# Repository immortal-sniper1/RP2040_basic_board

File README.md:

# RP2040_board1
 RP2040 test board, breadboard friedly.
 /
 Features: 
  /
 -Li ion power optin (protection built in) auto switching power in case of usb unpluging 
  /
 -RTC with separate 20mm cell  
 -microSD card slot  
 -all pins exposed (that are not used internaly for a dedicated task)  
 -both LDO and buck switching convertor for power, one of them may be used based on the SPDT switch  
 (later maybe just one of them may be populated and the switch replaced by a solder bridge)  
 -same pinout as rpi pico just wider form factor 
 -all pins labeled 
 -It requires a few extra wires to work since this is a 2 layer design and this was a scarifice
made in order to keep a solid ground plane under the entire PCB 
 
 Images:  https://imgur.com/a/X6zGeTy

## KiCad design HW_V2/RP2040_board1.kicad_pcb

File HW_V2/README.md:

# RP2040_board1
 RP2040 test board, breadboard friedly.  
 Features:   
 -Li ion power optin (protection built in) auto switching power in case of usb unpluging   
 -RTC with separate 20mm cell  
 -microSD card slot  
 -all pins exposed (that are not used internaly for a dedicated task)  
 -both LDO and buck switching convertor for power, one of them may be used based on the SPDT switch   
 (later maybe just one of them may be populated and the switch replaced by a solder bridge)   
 -same pinout as rpi pico just wider form factor   
 -all pins labeled   
 -It requires a few extra wires to work since this is a 2 layer design and this was a scarifice 
made in order to keep a solid ground plane under the entire PCB   
 
 Images:  https://imgur.com/a/X6zGeTy

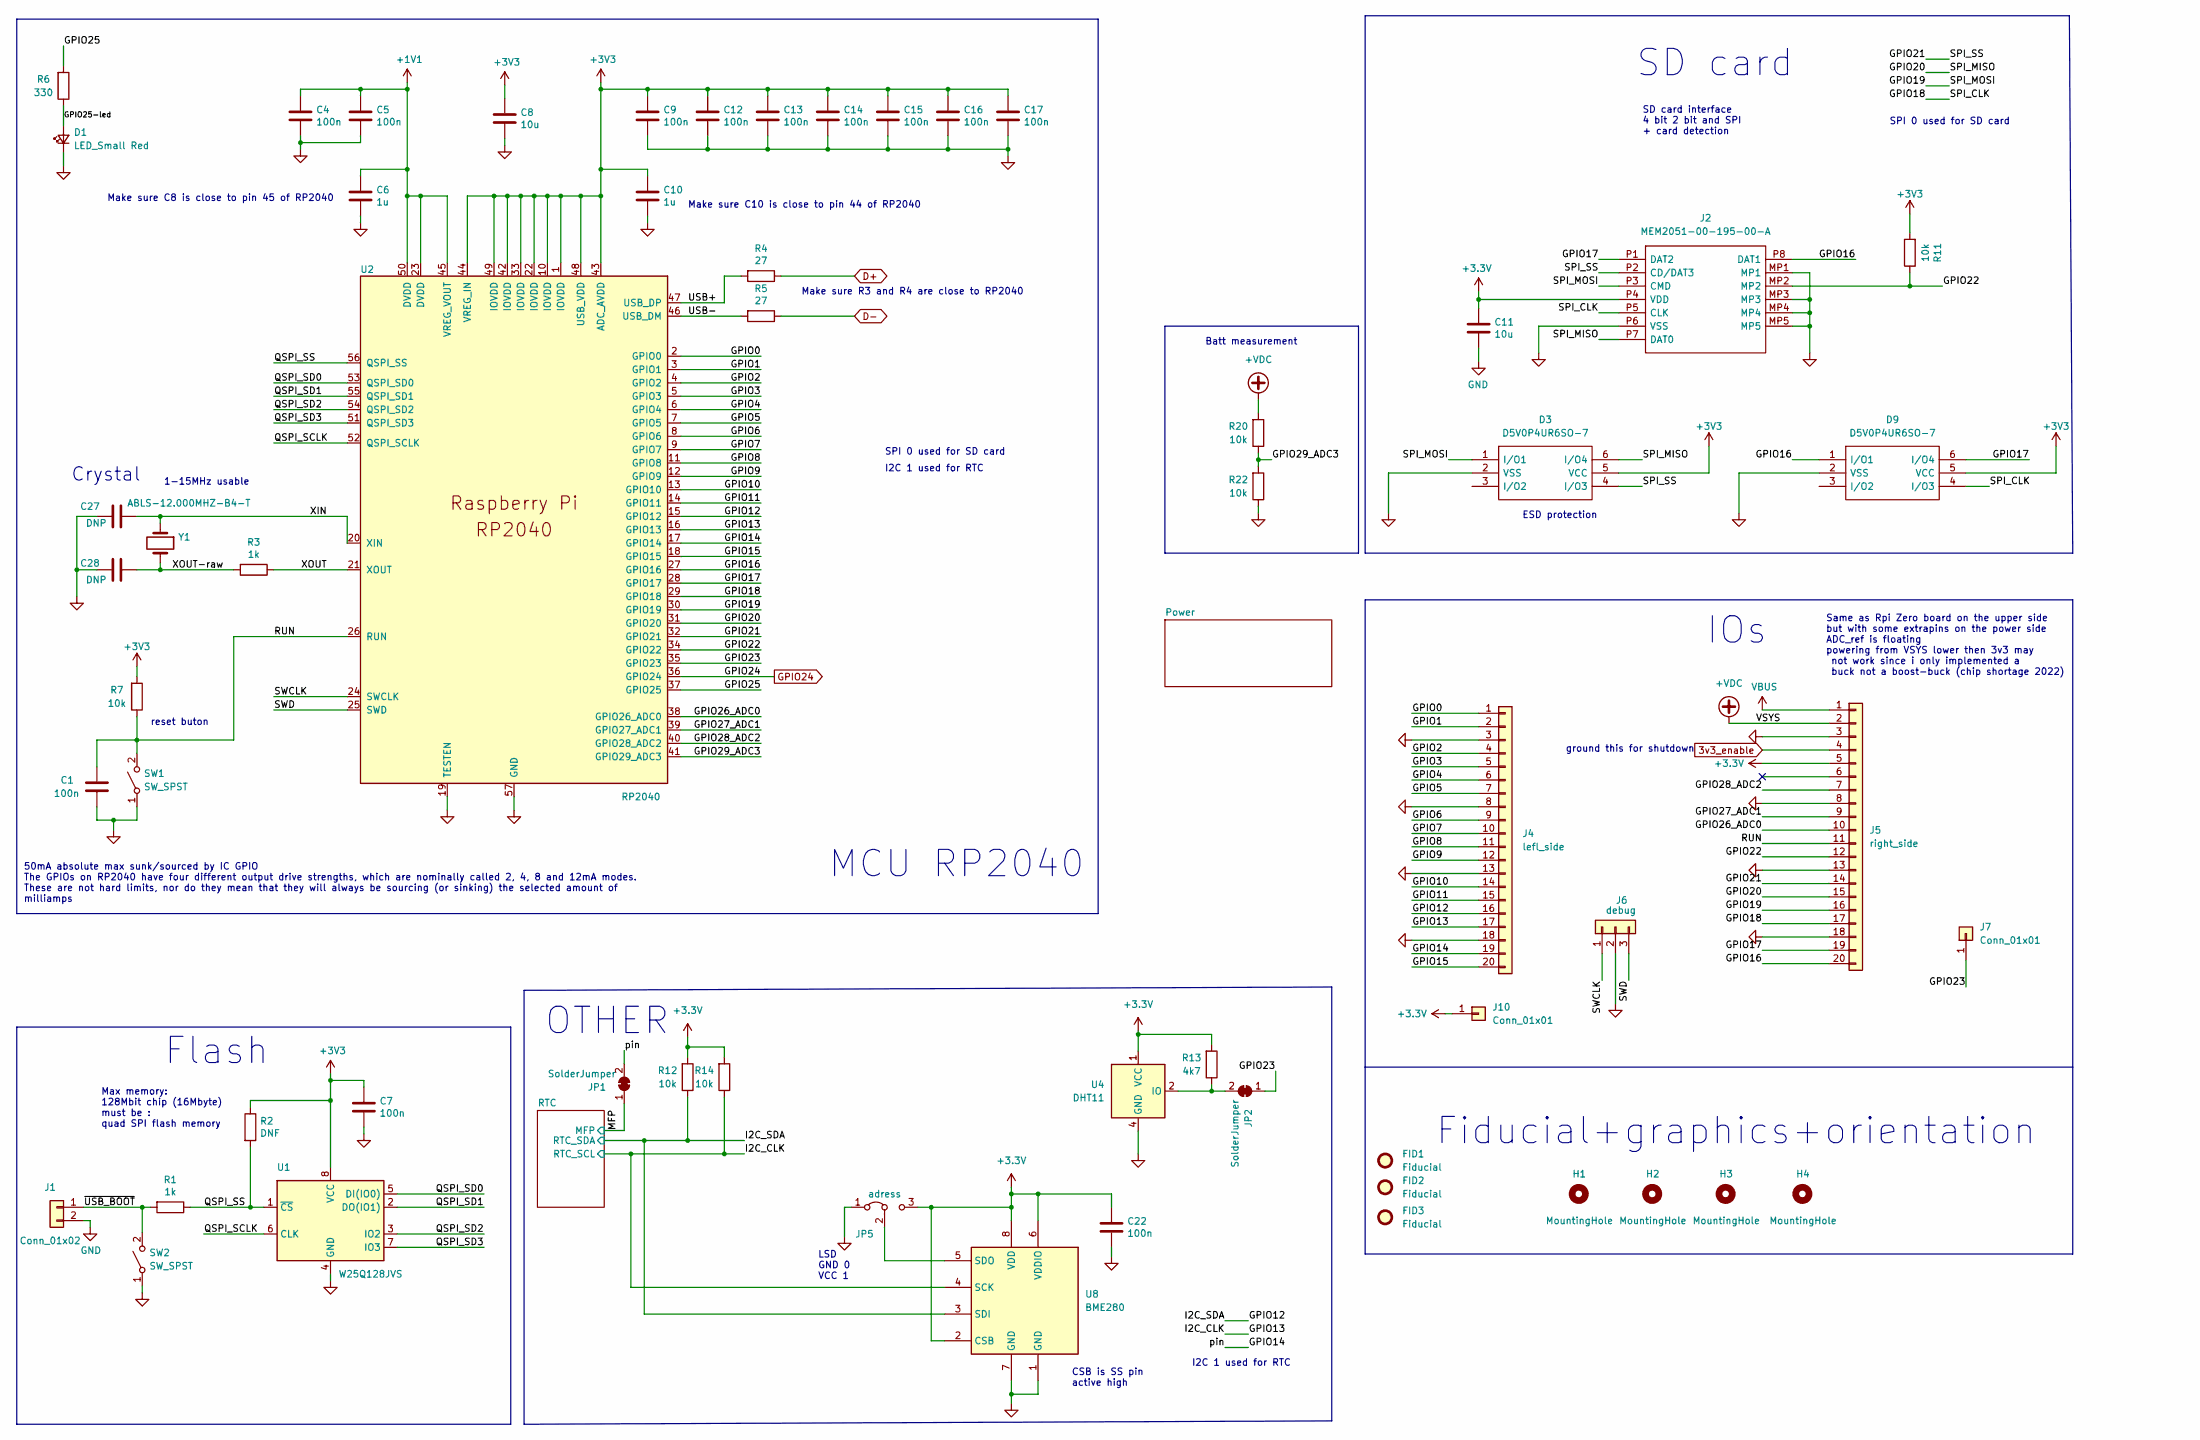
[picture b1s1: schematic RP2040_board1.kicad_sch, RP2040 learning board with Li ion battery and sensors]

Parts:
C1, C4, C5, C7, C9, C12, C13, C14, C15, C16, C17, C22: 100n; C_0805_2012Metric_Pad1.18x1.45mm_HandSolder
C6, C10: 1u; C_0805_2012Metric_Pad1.18x1.45mm_HandSolder
C8: 10u; C_0805_2012Metric_Pad1.18x1.45mm_HandSolder
C11: 10u; C_0603_1608Metric_Pad1.08x0.95mm_HandSolder
C27, C28: DNP; C_0805_2012Metric_Pad1.18x1.45mm_HandSolder
D1: LED_Small Red; LED_0603_1608Metric_Pad1.05x0.95mm_HandSolder
D3, D9: D5V0P4UR6SO-7; SOT95P285X140-6N; Mouser Part Number 621-D5V0P4UR6SO-7
FID1: Fiducial; Fiducial_0.5mm_Mask1mm
FID2: Fiducial; KiCad-Logo2_8mm_SilkScreen
FID3: Fiducial; OSHW-Logo2_14.6x12mm_SilkScreen
H1, H2, H3, H4: MountingHole; MountingHole_3.2mm_M3
J1: Conn_01x02; PinHeader_1x02_P2.54mm_Vertical
J2: MEM2051-00-195-00-A; MEM20510019500A; Mouser Part Number 640-MEM20510019500A
J4: lefl_side; PinSocket_1x20_P2.54mm_Vertical
J5: right_side; PinSocket_1x20_P2.54mm_Vertical
J6: debug; PinSocket_1x03_P2.54mm_Vertical
J7, J10: Conn_01x01; PinSocket_1x01_P2.54mm_Vertical
JP1, JP2: SolderJumper; SolderJumper-2_P1.3mm_Bridged_RoundedPad1.0x1.5mm
JP5: adress; SolderJumper-3_P1.3mm_Bridged12_RoundedPad1.0x1.5mm
R1, R3: 1k; R_0603_1608Metric_Pad0.98x0.95mm_HandSolder
R2: DNF; R_0603_1608Metric_Pad0.98x0.95mm_HandSolder
R4, R5: 27; R_0603_1608Metric_Pad0.98x0.95mm_HandSolder
R6: 330; R_0603_1608Metric_Pad0.98x0.95mm_HandSolder
R7, R11, R12, R14, R20, R22: 10k; R_0603_1608Metric_Pad0.98x0.95mm_HandSolder
R13: 4k7; R_0603_1608Metric_Pad0.98x0.95mm_HandSolder
SW1, SW2: SW_SPST; PTS526SK15SMTR2LFS
U1: W25Q128JVS; SOIC-8_5.23x5.23mm_P1.27mm
U2: RP2040; RP2040-QFN-56
U4: DHT11; Aosong_DHT11_5.5x12.0_P2.54mm
U8: BME280; Bosch_LGA-8_2.5x2.5mm_P0.65mm_ClockwisePinNumbering
Y1: ABLS-12.000MHZ-B4-T; ATS120SM

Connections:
3v3_enable: J5.4; also elsewhere on the board
+1V1: C4.1, C5.1, C6.1, U2.23 (DVDD), U2.45 (VREG_VOUT), U2.50 (DVDD)
+VDC: J5.2, R20.2; also elsewhere on the board
/GPIO0: J4.1, U2.2 (GPIO0)
/GPIO1: J4.2, U2.3 (GPIO1)
/GPIO2: J4.4, U2.4 (GPIO2)
/GPIO3: J4.5, U2.5 (GPIO3)
/GPIO4: J4.6, U2.6 (GPIO4)
/GPIO5: J4.7, U2.7 (GPIO5)
/GPIO6: J4.9, U2.8 (GPIO6)
/GPIO7: J4.10, U2.9 (GPIO7)
/GPIO8: J4.11, U2.11 (GPIO8)
/GPIO9: J4.12, U2.12 (GPIO9)
/GPIO10: J4.14, U2.13 (GPIO10)
/GPIO11: J4.15, U2.14 (GPIO11)
/GPIO12: J4.16, R12.1, U2.15 (GPIO12), U8.3 (SDI); also elsewhere on the board
/GPIO13: J4.17, R14.1, U2.16 (GPIO13), U8.4 (SCK); also elsewhere on the board
/GPIO14: J4.19, JP1.2 (B), U2.17 (GPIO14)
/GPIO15: J4.20, U2.18 (GPIO15)
/GPIO16: D9.1 (I/O1), J2.P8 (DAT1), J5.20, U2.27 (GPIO16)
/GPIO17: D9.6 (I/O4), J2.P1 (DAT2), J5.19, U2.28 (GPIO17)
/GPIO18: D9.4 (I/O3), J2.P5 (CLK), J5.17, U2.29 (GPIO18)
/GPIO19: D3.1 (I/O1), J2.P3 (CMD), J5.16, U2.30 (GPIO19)
/GPIO20: D3.6 (I/O4), J2.P7 (DAT0), J5.15, U2.31 (GPIO20)
/GPIO21: D3.4 (I/O3), J2.P2 (CD/DAT3), J5.14, U2.32 (GPIO21)
/GPIO22: J2.MP2, J5.12, R11.1, U2.34 (GPIO22)
/GPIO23: J7.1, JP2.1 (A), U2.35 (GPIO23)
/GPIO25: R6.2, U2.37 (GPIO25)
/GPIO25-led: D1.2 (A), R6.1
/GPIO26_ADC0: J5.10, U2.38 (GPIO26_ADC0)
/GPIO27_ADC1: J5.9, U2.39 (GPIO27_ADC1)
/GPIO28_ADC2: J5.7, U2.40 (GPIO28_ADC2)
/GPIO29_ADC3: R20.1, R22.2, U2.41 (GPIO29_ADC3)
/MFP: JP1.1 (A); also elsewhere on the board
/QSPI_SCLK: U1.6 (CLK), U2.52 (QSPI_SCLK)
/QSPI_SD0: U1.5 (DI(IO0)), U2.53 (QSPI_SD0)
/QSPI_SD1: U1.2 (DO(IO1)), U2.55 (QSPI_SD1)
/QSPI_SD2: U1.3 (IO2), U2.54 (QSPI_SD2)
/QSPI_SD3: U1.7 (IO3), U2.51 (QSPI_SD3)
/QSPI_SS: R1.1, R2.2, U1.1 (~CS), U2.56 (QSPI_SS)
/RUN: C1.1, J5.11, R7.1, SW1.2 (B), U2.26 (RUN)
/SWCLK: J6.1, U2.24 (SWCLK)
/SWD: J6.3, U2.25 (SWD)
/USB+: R4.2, U2.47 (USB_DP)
/USB-: R5.2, U2.46 (USB_DM)
/XIN: C27.2, U2.20 (XIN), Y1.1
/XOUT: R3.1, U2.21 (XOUT)
/XOUT-raw: C28.2, R3.2, Y1.2
/~USB_BOOT: J1.1, R1.2, SW2.2 (B)
D+: R4.1; also elsewhere on the board
D-: R5.1; also elsewhere on the board
GND: C1.2, C4.2, C5.2, C6.2, C7.2, C8.2, C9.2, C10.2, C11.2, C12.2, C13.2, C14.2, C15.2, C16.2, C17.2, C22.2, C27.1, C28.1, D1.1 (K), D3.2 (VSS), D9.2 (VSS), J1.2, J2.MP1, J2.MP3, J2.MP4, J2.MP5, J2.P6 (VSS), J4.3, J4.8, J4.13, J4.18, J5.3, J5.8, J5.13, J5.18, J6.2, JP5.1 (A), R22.1, SW1.1 (A), SW2.1 (A), U1.4 (GND), U2.19 (TESTEN), U2.57 (GND), U4.4 (GND), U8.1 (GND), U8.7 (GND); also elsewhere on the board
GPIO24: U2.36 (GPIO24); also elsewhere on the board
unnamed: JP2.2 (B), R13.1, U4.2 (IO)
unnamed: JP5.2 (C), U8.5 (SDO)
VBUS: J5.1; also elsewhere on the board

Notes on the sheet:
I2C 1 used for RTC
Fiducial+graphics+orientation
SD card interface 4 bit 2 bit and SPI + card detection
OTHER
50mA absolute max sunk/sourced by IC GPIO The GPIOs on RP2040 have four different output drive strengths, which are nominally called 2, 4, 8 and 12mA modes. These are not hard limits, nor do they mean that they will always be sourcing (or sinking) the selected amount of milliamps
IOs
Same as Rpi Zero board on the upper side but with some extrapins on the power side ADC_ref is floating powering from VSYS lower then 3v3 may not work since i only implemented a buck not a boost-buck (chip shortage 2022)
Flash
ground this for shutdown
Crystal
SD card
MCU RP2040
Make sure C8 is close to pin 45 of RP2040
SPI 0 used for SD card
Make sure R3 and R4 are close to RP2040
Max memory: 128Mbit chip (16Mbyte) must be : quad SPI flash memory
1-15MHz usable
Make sure C10 is close to pin 44 of RP2040
reset buton
LSD GND 0 VCC 1
ESD protection
Batt measurement
CSB is SS pin active high

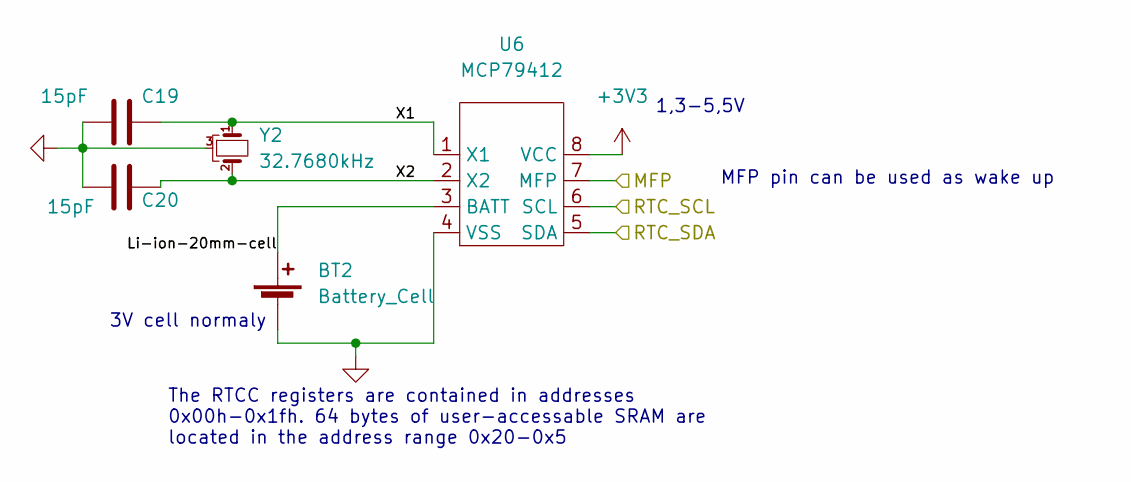
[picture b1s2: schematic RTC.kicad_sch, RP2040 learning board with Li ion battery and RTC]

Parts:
BT2: Battery_Cell; BATHLD001THM
C19, C20: 15pF; C_0603_1608Metric_Pad1.08x0.95mm_HandSolder
U6: MCP79412; TSSOP-8_4.4x3mm_P0.65mm
Y2: 32.7680kHz; Crystal_C38-LF_D3.0mm_L8.0mm_Vertical

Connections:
/GPIO12: U6.5 (SDA); also elsewhere on the board
/GPIO13: U6.6 (SCL); also elsewhere on the board
/MFP: U6.7 (MFP); also elsewhere on the board
/RTC/Li-ion-20mm-cell: BT2.1 (+), U6.3 (BATT)
/RTC/X1: C19.2, U6.1 (X1), Y2.1
/RTC/X2: C20.2, U6.2 (X2), Y2.2
GND: BT2.2 (-), C19.1, C20.1, U6.4 (VSS), Y2.3; also elsewhere on the board

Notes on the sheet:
1,3-5,5V
3V cell normaly
MFP pin can be used as wake up
The RTCC registers are contained in addresses 0x00h-0x1fh. 64 bytes of user-accessable SRAM are located in the address range 0x20-0x5

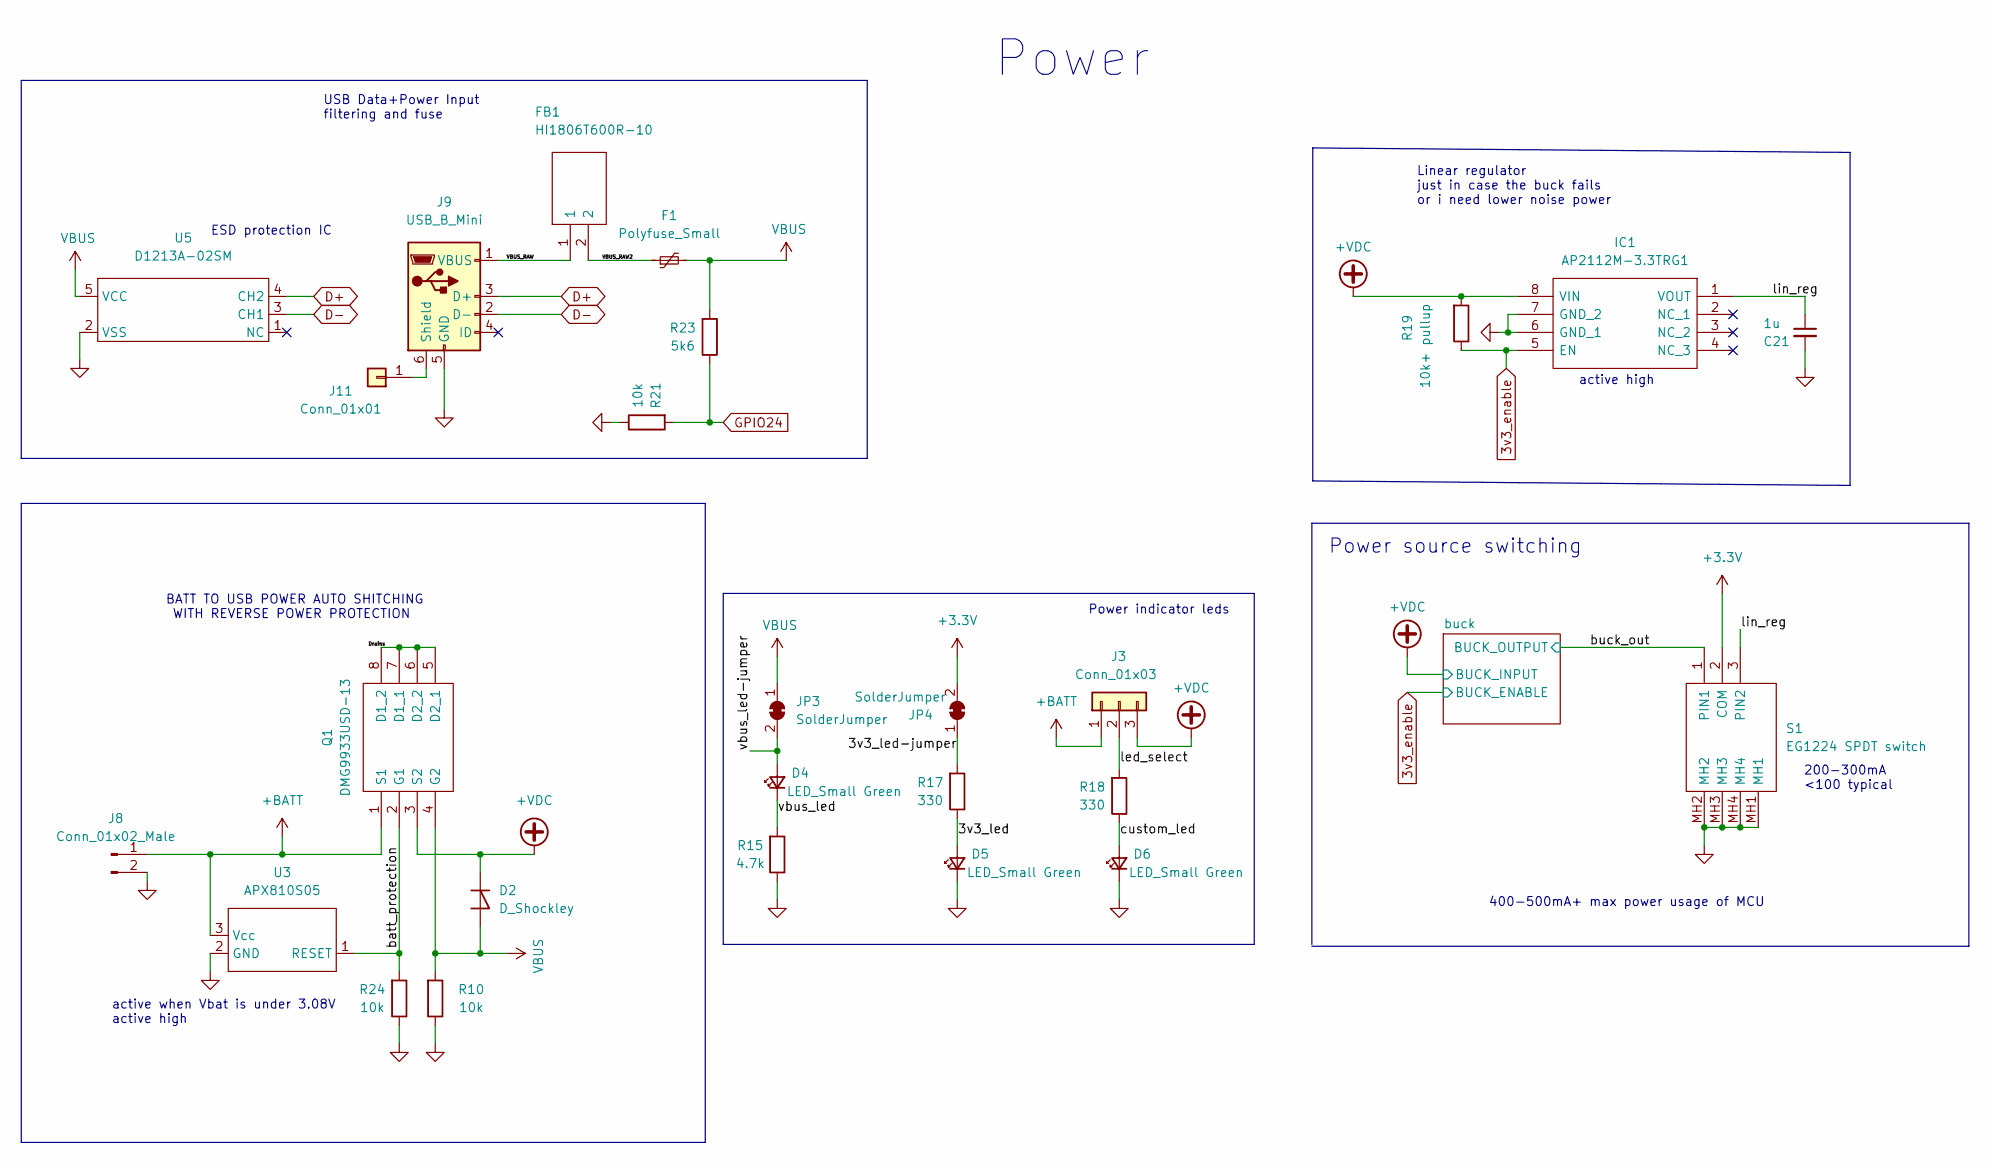
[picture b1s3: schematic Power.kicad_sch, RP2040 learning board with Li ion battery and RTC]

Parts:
C21: 1u; C_0805_2012Metric_Pad1.18x1.45mm_HandSolder
D2: D_Shockley; D_DO-15_P5.08mm_Vertical_KathodeUp
D4, D5, D6: LED_Small Green; LED_0603_1608Metric_Pad1.05x0.95mm_HandSolder
F1: Polyfuse_Small; Fuse_1812_4532Metric_Pad1.30x3.40mm_HandSolder
FB1: HI1806T600R-10; BEADC4516X185N; Mouser Part Number 875-HI1806T600R-10
IC1: AP2112M-3.3TRG1; SOIC127P600X170-8N; Mouser Part Number 621-AP2112M-3.3TRG1
J3: Conn_01x03; PinHeader_1x03_P2.54mm_Vertical
J8: Conn_01x02_Male; PinHeader_1x02_P2.54mm_Vertical
J9: USB_B_Mini; USB_Mini-B_Lumberg_2486_01_Horizontal
J11: Conn_01x01; PinSocket_1x01_P2.54mm_Vertical
JP3, JP4: SolderJumper; SolderJumper-2_P1.3mm_Bridged_RoundedPad1.0x1.5mm
Q1: DMG9933USD-13; SOIC127P600X175-8N; Mouser Part Number 621-DMG9933USD-13
R10, R21, R24: 10k; R_0603_1608Metric_Pad0.98x0.95mm_HandSolder
R15: 4.7k; R_Axial_DIN0204_L3.6mm_D1.6mm_P5.08mm_Vertical
R17, R18: 330; R_0603_1608Metric_Pad0.98x0.95mm_HandSolder
R19: 10k+ pullup; R_0603_1608Metric_Pad0.98x0.95mm_HandSolder
R23: 5k6; R_0603_1608Metric_Pad0.98x0.95mm_HandSolder
S1: EG1224 SPDT switch; EG1224; Mouser Part Number 612-EG1224
U3: APX810S05; SOT-23
U5: D1213A-02SM; SOT-23-5_HandSoldering

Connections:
3v3_enable: IC1.5 (EN), R19.1; also elsewhere on the board
+BATT: J3.1, J8.1, Q1.1 (S1), U3.3 (Vcc); also elsewhere on the board
+VDC: D2.1 (K), IC1.8 (VIN), J3.3, Q1.3 (S2), R19.2; also elsewhere on the board
/Power/3v3_led: D5.2 (A), R17.1
/Power/3v3_led-jumper: JP4.1 (A), R17.2
/Power/VBUS_RAW: FB1.1, J9.1 (VBUS)
/Power/VBUS_RAW2: F1.1, FB1.2
/Power/batt_protection: Q1.2 (G1), R24.2, U3.1 (RESET); also elsewhere on the board
/Power/buck_out: S1.1 (PIN1); also elsewhere on the board
/Power/custom_led: D6.2 (A), R18.1
/Power/led_select: J3.2, R18.2
/Power/lin_reg: C21.1, IC1.1 (VOUT), S1.3 (PIN2)
/Power/vbus_led: D4.1 (K), R15.2
/Power/vbus_led-jumper: D4.2 (A), JP3.2 (B)
D+: J9.3 (D+), U5.4 (CH2); also elsewhere on the board
D-: J9.2 (D-), U5.3 (CH1); also elsewhere on the board
GND: C21.2, D5.1 (K), D6.1 (K), IC1.6 (GND_1), IC1.7 (GND_2), J8.2, J9.5 (GND), R10.1, R15.1, R21.1, R24.1, S1.MH1, S1.MH2, S1.MH3, S1.MH4, U3.2 (GND), U5.2 (VSS); also elsewhere on the board
GPIO24: R21.2, R23.1; also elsewhere on the board
unnamed: J9.6 (Shield), J11.1
unnamed: Q1.5 (D2_1), Q1.6 (D2_2), Q1.7 (D1_1), Q1.8 (D1_2)
VBUS: D2.2 (A), F1.2, JP3.1 (A), Q1.4 (G2), R10.2, R23.2, U5.5 (VCC); also elsewhere on the board

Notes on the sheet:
400-500mA+ max power usage of MCU
ESD protection IC
active when Vbat is under 3.08V active high
Power indicator leds
Linear regulator just in case the buck fails or i need lower noise power
200-300mA <100 typical
USB Data+Power Input filtering and fuse
Power source switching
Power
active high
BATT TO USB POWER AUTO SHITCHING WITH REVERSE POWER PROTECTION

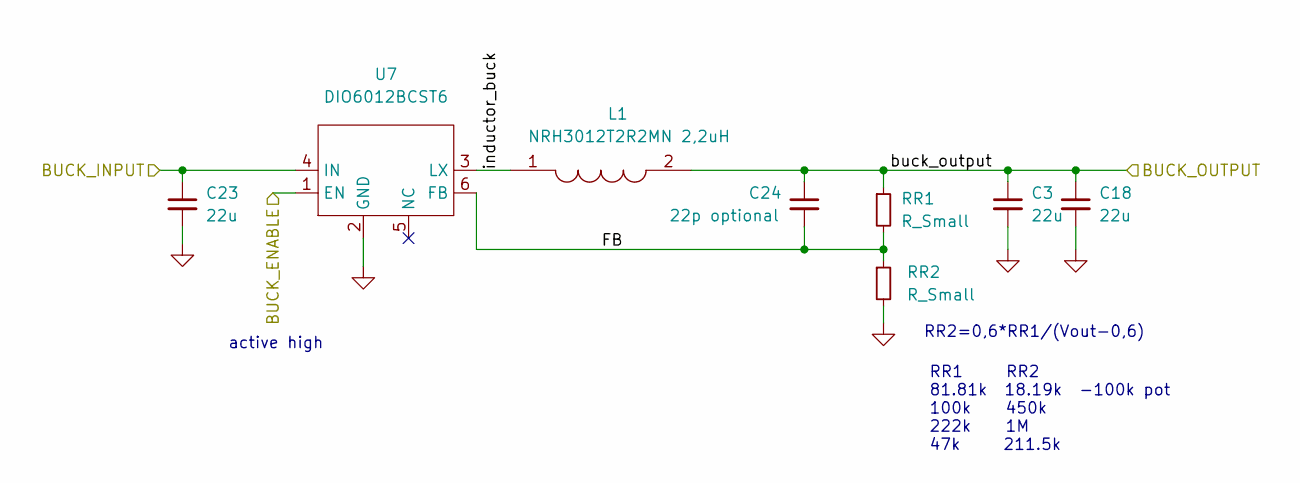
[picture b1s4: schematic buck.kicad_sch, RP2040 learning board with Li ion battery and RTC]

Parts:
C3, C18, C23: 22u; CP_Radial_D5.0mm_P2.00mm
C24: 22p optional; C_0603_1608Metric_Pad1.08x0.95mm_HandSolder
L1: NRH3012T2R2MN 2,2uH; NRH3012T220MNV; Mouser Part Number 963-NRH3012T2R2MN
RR1, RR2: R_Small; R_Axial_DIN0204_L3.6mm_D1.6mm_P5.08mm_Vertical
U7: DIO6012BCST6; SOT-23-6_Handsoldering

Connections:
3v3_enable: U7.1 (EN); also elsewhere on the board
+VDC: C23.1, U7.4 (IN); also elsewhere on the board
/Power/buck/FB: C24.2, RR1.2, RR2.1, U7.6 (FB)
/Power/buck/inductor_buck: L1.1, U7.3 (LX)
/Power/buck_out: C3.1, C18.1, C24.1, L1.2, RR1.1; also elsewhere on the board
GND: C3.2, C18.2, C23.2, RR2.2, U7.2 (GND); also elsewhere on the board

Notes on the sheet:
RR2=0,6*RR1/(Vout-0,6)
active high
RR1 RR2 81.81k 18.19k -100k pot 100k 450k 222k 1M 47k 211.5k

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
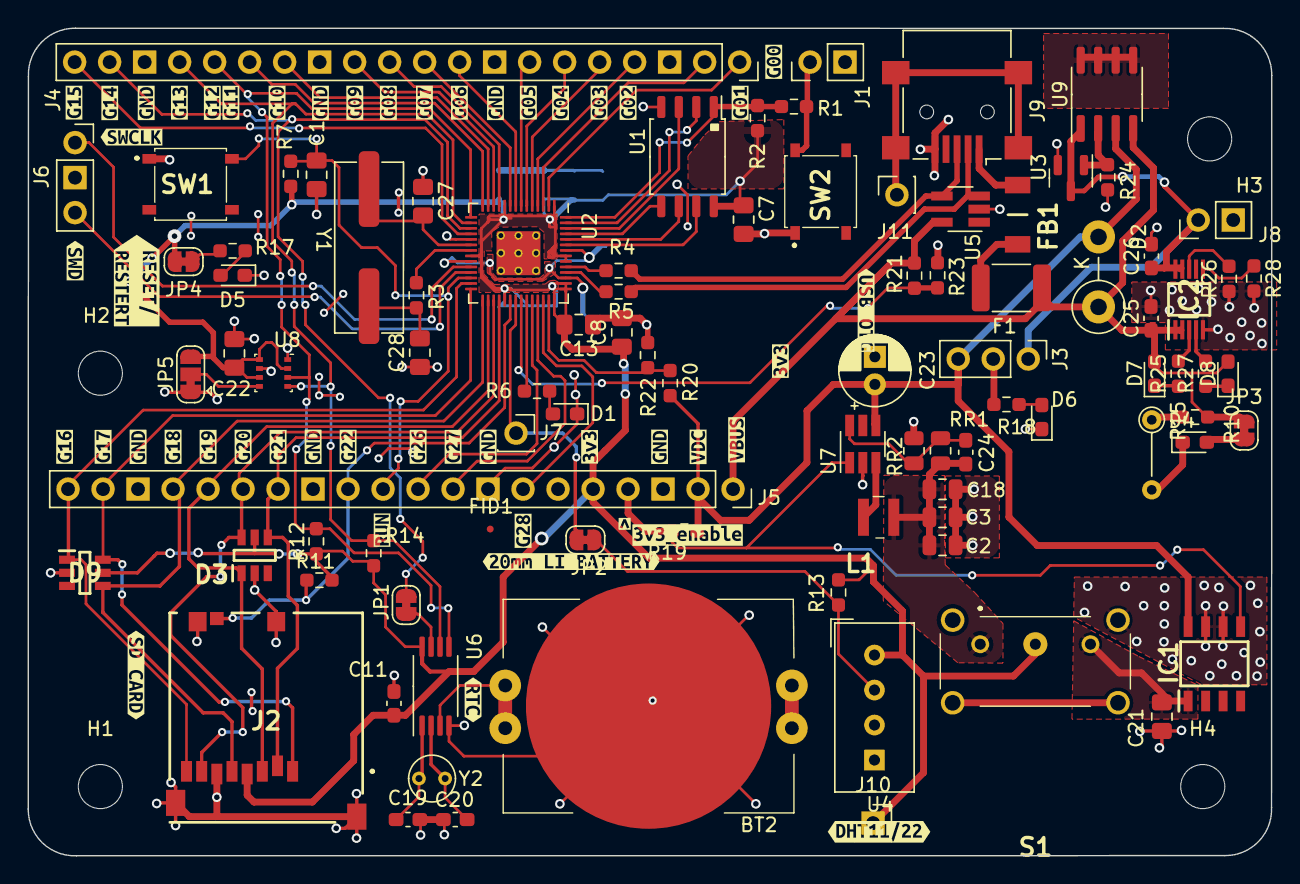
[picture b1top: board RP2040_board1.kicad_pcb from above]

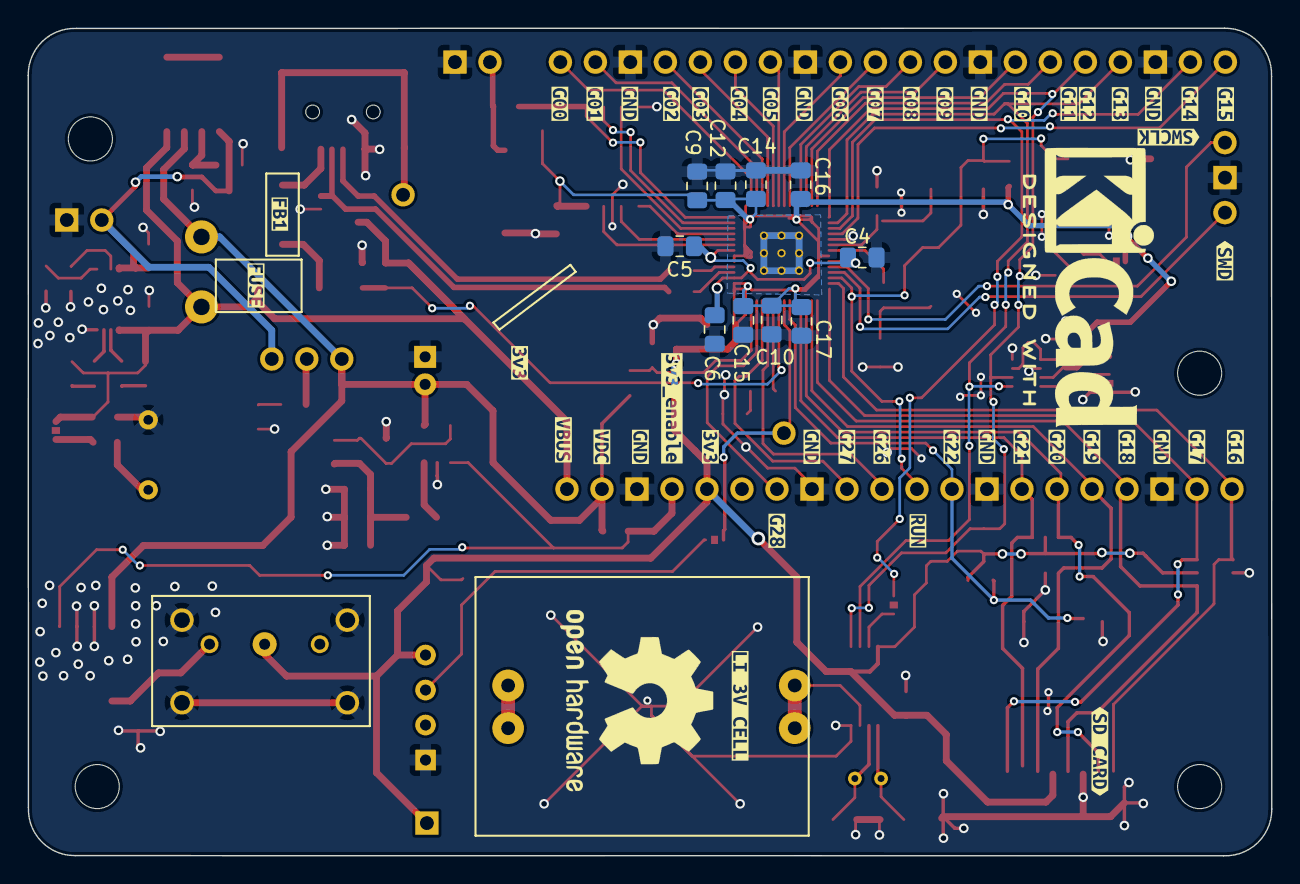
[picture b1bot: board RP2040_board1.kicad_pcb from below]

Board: 2 copper layers, 90.2 x 60.1 mm, 204 parts (61 on the bottom side), 82 nets.

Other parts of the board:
 : LOGO
C2: 10u; C_0805_2012Metric
C25: 1u; C_0603_1608Metric_Pad1.08x0.95mm_HandSolder
C26: 4.7u; C_0603_1608Metric_Pad1.08x0.95mm_HandSolder
D7, D8: LED_Small; LED_0603_1608Metric_Pad1.05x0.95mm_HandSolder
IC2: MCP73834T-FCI_UN; SOP50P490X110-10N
R25, R27: 470; R_0603_1608Metric_Pad0.98x0.95mm_HandSolder
R26, R28: 10k; R_0603_1608Metric_Pad0.98x0.95mm_HandSolder
U9: DMG9933USD-13; SOIC-8_3.9x4.9mm_P1.27mm
kibuzzard-626E75F6, kibuzzard-626E75F6#2: G***; kibuzzard-626E75F6
kibuzzard-626E76A5, kibuzzard-626E76A5#2: G***; kibuzzard-626E76A5
kibuzzard-626E76AE, kibuzzard-626E76AE#2: G***; kibuzzard-626E76AE
kibuzzard-626E76B5, kibuzzard-626E76B5#2: G***; kibuzzard-626E76B5
kibuzzard-626E76C0, kibuzzard-626E76C0#2: G***; kibuzzard-626E76C0
kibuzzard-626E76C6, kibuzzard-626E76C6#2: G***; kibuzzard-626E76C6
kibuzzard-626E76CD, kibuzzard-626E76CD#2: G***; kibuzzard-626E76CD
kibuzzard-626E76D2, kibuzzard-626E76D2#2: G***; kibuzzard-626E76D2
kibuzzard-626E76E0, kibuzzard-626E76E0#2: G***; kibuzzard-626E76E0
kibuzzard-626E76E7, kibuzzard-626E76E7#2: G***; kibuzzard-626E76E7
kibuzzard-626E94A4: G***; kibuzzard-626E94A4
kibuzzard-626E96A8, kibuzzard-626E96A8#2: G***; kibuzzard-626E96A8
kibuzzard-626E96B6, kibuzzard-626E96B6#2, kibuzzard-626E96B6#3, kibuzzard-626E96B6#4: G***; kibuzzard-626E96B6
kibuzzard-626E96C2, kibuzzard-626E96C2#2: G***; kibuzzard-626E96C2
kibuzzard-626E96E0: G***; kibuzzard-626E96E0
kibuzzard-626E96EE, kibuzzard-626E96EE#2: G***; kibuzzard-626E96EE
kibuzzard-626E96FC, kibuzzard-626E96FC#2: G***; kibuzzard-626E96FC
kibuzzard-626E98D2, kibuzzard-626E98D2#2: G***; kibuzzard-626E98D2
kibuzzard-626E760F, kibuzzard-626E760F#2: G***; kibuzzard-626E760F
kibuzzard-626E761A, kibuzzard-626E761A#2: G***; kibuzzard-626E761A
kibuzzard-626E769F, kibuzzard-626E769F#2: G***; kibuzzard-626E769F
kibuzzard-626E937A: G***; kibuzzard-626E937A
kibuzzard-626E946D: G***; kibuzzard-626E946D
kibuzzard-626E948F: G***; kibuzzard-626E948F
kibuzzard-626E966C, kibuzzard-626E966C#2: G***; kibuzzard-626E966C
kibuzzard-626E968A, kibuzzard-626E968A#2: G***; kibuzzard-626E968A
kibuzzard-626E969D, kibuzzard-626E969D#2: G***; kibuzzard-626E969D
kibuzzard-626E977A, kibuzzard-626E977A#2: G***; kibuzzard-626E977A
kibuzzard-626E7343, kibuzzard-626E7343#2: G***; kibuzzard-626E7343
kibuzzard-626E7607, kibuzzard-626E7607#2, kibuzzard-626E7607#3, kibuzzard-626E7607#4, kibuzzard-626E7607#5, kibuzzard-626E7607#6, kibuzzard-626E7607#7, kibuzzard-626E7607#8, kibuzzard-626E7607#9, kibuzzard-626E7607#10, kibuzzard-626E7607#11, kibuzzard-626E7607#12, kibuzzard-626E7607#13, kibuzzard-626E7607#14, kibuzzard-626E7607#15: G***; kibuzzard-626E7607
kibuzzard-626E7622, kibuzzard-626E7622#2: G***; kibuzzard-626E7622
kibuzzard-626E7694, kibuzzard-626E7694#2: G***; kibuzzard-626E7694
kibuzzard-626E9458, kibuzzard-626E9458#2: G***; kibuzzard-626E9458
kibuzzard-626E9527, kibuzzard-626E9527#2: G***; kibuzzard-626E9527
kibuzzard-626E9537, kibuzzard-626E9537#2: G***; kibuzzard-626E9537
kibuzzard-626E9677, kibuzzard-626E9677#2: G***; kibuzzard-626E9677
kibuzzard-626E9683, kibuzzard-626E9683#2: G***; kibuzzard-626E9683
kibuzzard-626E9692, kibuzzard-626E9692#2: G***; kibuzzard-626E9692
kibuzzard-626ED31B, kibuzzard-626ED31B#2: G***; kibuzzard-626ED31B
kibuzzard-626ED41E: G***; kibuzzard-626ED41E
kibuzzard-626ED45F: G***; kibuzzard-626ED45F
kibuzzard-626ED354, kibuzzard-626ED354#2: G***; kibuzzard-626ED354
kibuzzard-626ED435: G***; kibuzzard-626ED435
kibuzzard-626ED447: G***; kibuzzard-626ED447
kibuzzard-627E9976: G***; kibuzzard-627E9976
kibuzzard-6275430A: G***; kibuzzard-6275430A

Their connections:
+BATT: C26.1, IC2.9 (VBAT_1), IC2.10 (VBAT_2), U9.1 (S); also elsewhere on the board
+VDC: U9.3 (S); also elsewhere on the board
/Power/Drains: U9.5 (D), U9.6 (D), U9.7 (D), U9.8 (D)
/Power/Set_charge_current: IC2.6 (PROG), R28.1
/Power/batt_protection: U9.2 (G); also elsewhere on the board
/Power/buck_out: C2.1; also elsewhere on the board
GND: C2.2, C25.2, C26.2, IC2.5 (VSS), R26.1, R28.2; also elsewhere on the board
unnamed: D7.1 (K), R25.1
unnamed: D8.1 (K), R27.1
unnamed: IC2.3 (STAT1), R25.2
unnamed: IC2.4 (STAT2), R27.2
unnamed: IC2.8 (THERM), R26.2
VBUS: C25.1, D7.2 (A), D8.2 (A), IC2.1 (VDD_1), IC2.2 (VDD_2), U9.4 (G); also elsewhere on the board

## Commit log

2022-04-30 ver1
2022-05-01 silkscreen
2022-06-05 Update fp-info-cache
